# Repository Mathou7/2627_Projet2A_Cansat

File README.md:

# 2627_Projet2A_Cansat

Projet Cansat de 2A

## Partie Info

### Tableau Récapitulatif des connexions entre composants

| Broche STM32 | Signal | Élément / Périphérique | Protocole / Rôle | Adresse I2C |
| --- | --- | --- | --- | --- |
| **PA0** | `PWM` | Connecteur Moteur | Sortie PWM (+5V) | — |
| **PA1** | `MesBat` | Mesure Batterie (Pont diviseur) | Entrée analogique (ADC) | — |
| **PA2** / **PA3** | `VCP_RX` / `VCP_TX` | ST-LINK / Liaison série (Virtual COM) | UART | — |
| **PA4** | `INT_IMU` | Centrale Inertielle **BNO055** | Interruption matérielle | **`0x29`** (ou `0x28`) |
| **PA5** | `INT_BARO` | Capteur de pression **BMP581** | Interruption matérielle | **`0x46`** (ou `0x47`) |
| **PB0** | `CS_SD` | Port MicroSD (Chip Select) | GPIO / SPI | — |
| **PB3** | `SPI_SCK` | Port MicroSD (Horloge SPI) | SPI (Horloge) | — |
| **PB4** | `MISO` | Port MicroSD (Master In Slave Out) | SPI | — |
| **PB5** | `MOSI` | Port MicroSD (Master Out Slave In) | SPI | — |
| **PA9** | `SCL` | Bus I2C Commun (**BNO055** & **BMP581**) | I2C (Horloge avec pull-up) | Partagé |
| **PA8** | `SDA` | Bus I2C Commun (**BNO055** & **BMP581**) | I2C (Données avec pull-up) | Partagé |
| **PG10** | `NRST` | Bouton de Reset / Réinitialisation | Reset matériel | — |
| **PA13** / **PA14** | `SWDIO` / `SWCLK` | Connecteur ST-LINK (Debug / Programmation) | SWD | — |

## Tableau Récapitulatif du RTOS

| Tâche FreeRTOS | Rôle | Périodicité / Déclenchement | Priorité | Taille de Pile |
| --- | --- | --- | --- | --- |
| **`SensorTask`** | Acquisition I2C de la centrale BNO055 et du baromètre BMP581 | Périodique rigoureuse (ex: **20 ms / 50 Hz**) | **Haute** (ou *Normal* haute) | 512 mots (*words*) |
| **`LoggingTask`** | Enregistrement des données sur la carte MicroSD via le bus SPI | Sur événement (bloquée en attente via une Queue) | **Basse** (*Below Normal*) | 512 mots (*words*) |
| **`ControlTask`** | Surveillance de la tension batterie (ADC) et gestion de la PWM moteur | Périodique (ex: **100 ms / 10 Hz**) | **Normale** (*Normal*) | 512 mots (*words*) |

## Pinout STM32G431KBT6

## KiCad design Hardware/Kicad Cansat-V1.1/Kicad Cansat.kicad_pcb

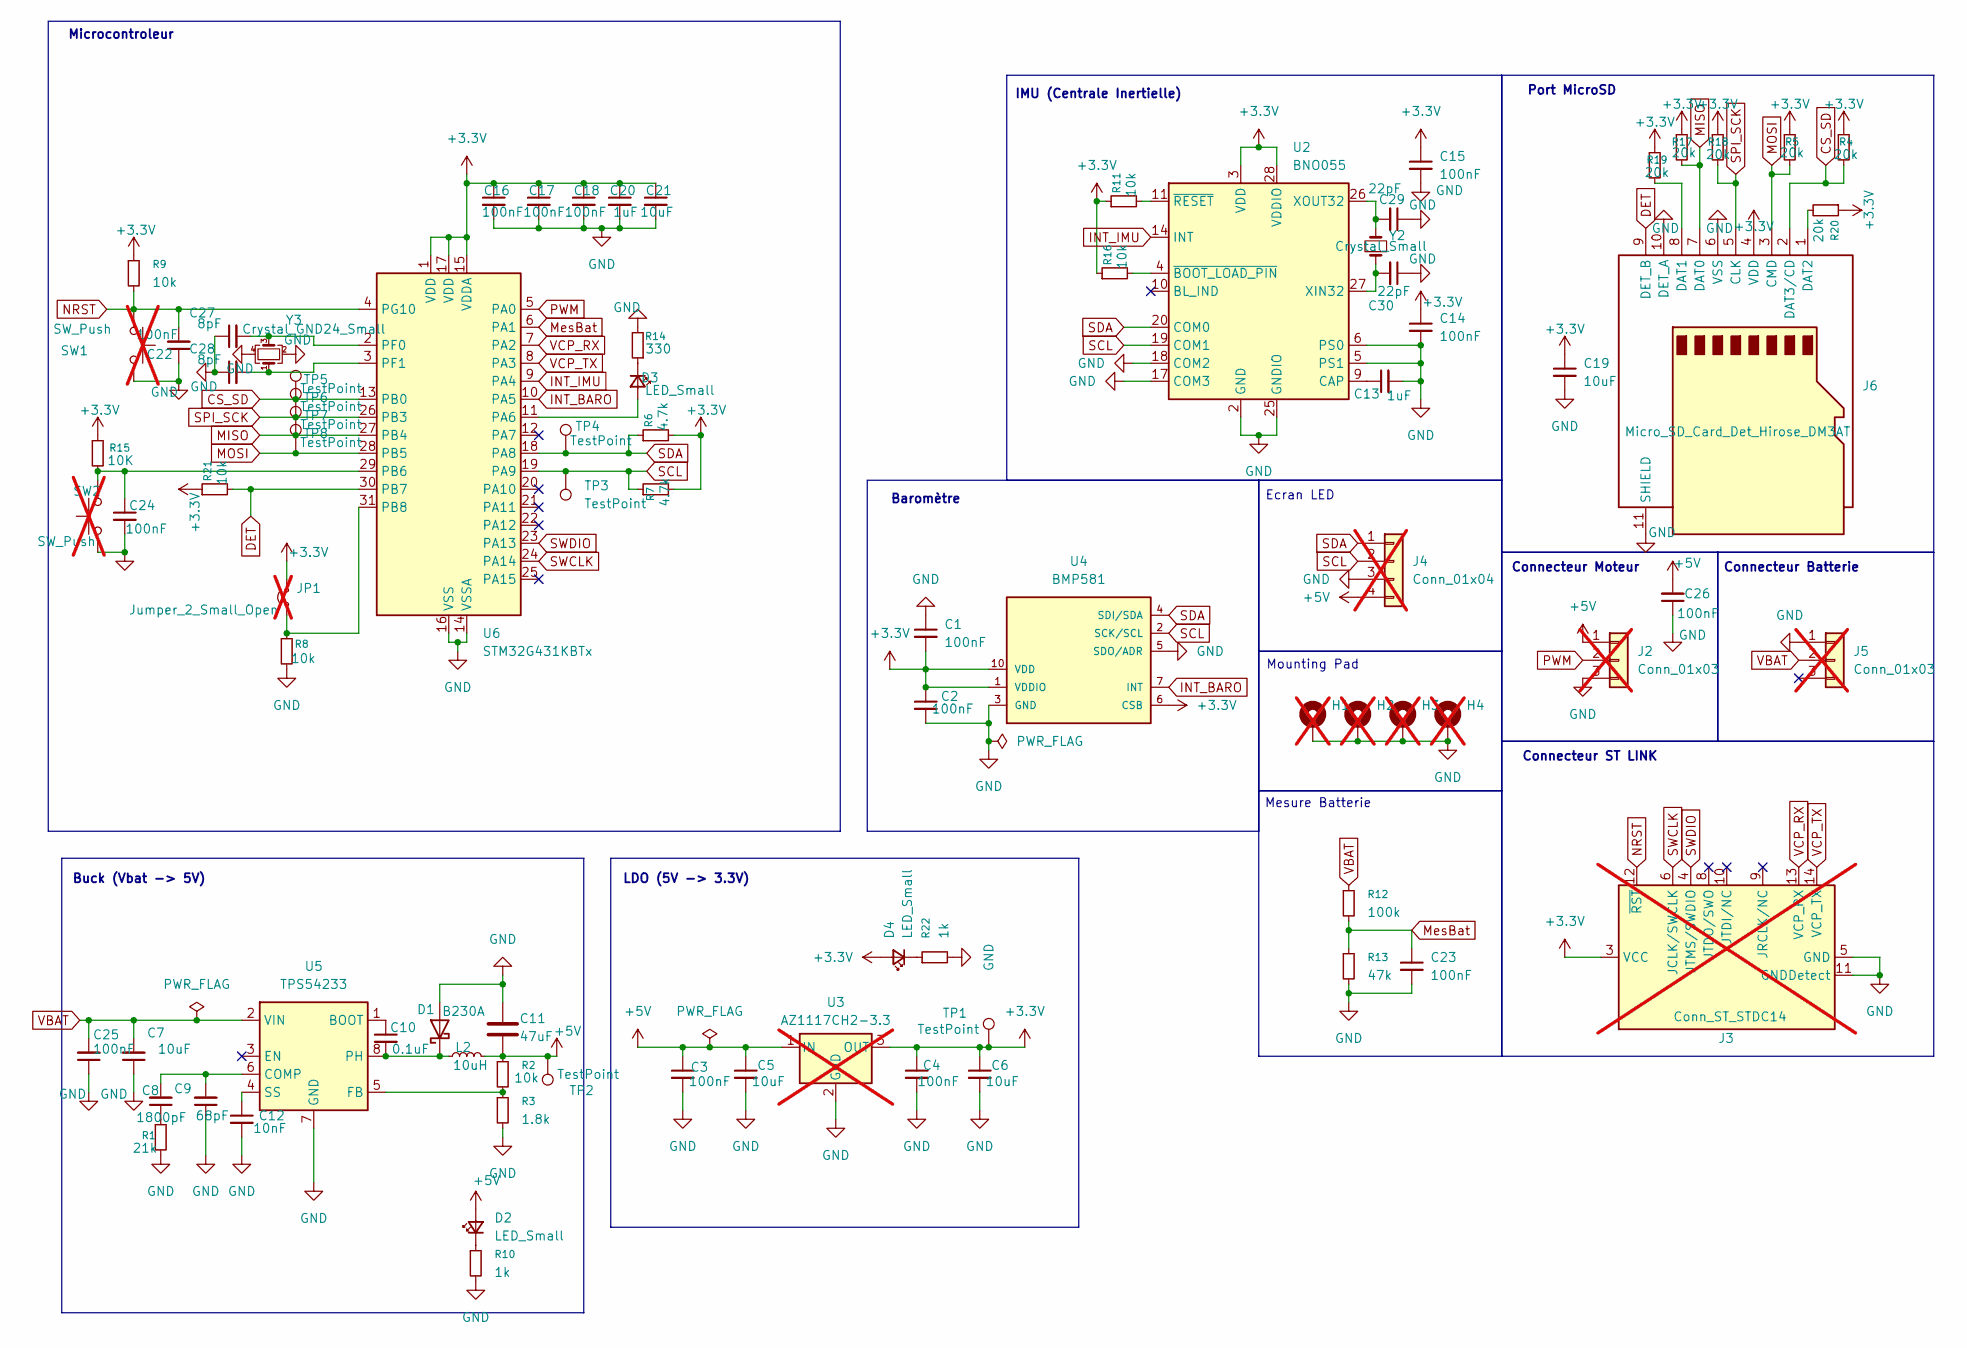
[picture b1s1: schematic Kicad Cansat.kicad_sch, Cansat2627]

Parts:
C1, C2, C3, C4, C14, C15, C16, C17, C18, C22, C23, C24, C25, C26: 100nF; C_0603_1608Metric; JLCPCB Part # C14663
C5, C6, C19, C21: 10uF; C_0603_1608Metric; JLCPCB Part # C19702
C7: 10uF; C_0805_2012Metric; JLCPCB Part # C15850
C8: 1800pF; C_0603_1608Metric; JLCPCB Part # C1604
C9: 68pF; C_0603_1608Metric; JLCPCB Part # C14858
C10: 0.1uF; C_0603_1608Metric; JLCPCB Part # C14663
C11: 47uF; C_1206_3216Metric; JLCPCB Part # C96123
C12: 10nF; C_0603_1608Metric; JLCPCB Part # C57112
C13, C20: 1uF; C_0603_1608Metric; JLCPCB Part # C15849
C27, C28: 8pF; C_0603_1608Metric; JLCPCB Part # C1634
C29, C30: 22pF; C_0603_1608Metric; JLCPCB Part # C1653
D1: B230A; D_SMA; JLCPCB Part # C22430
D2, D3, D4: LED_Small; LED_0603_1608Metric; JLCPCB Part # C2286
H1, H2, H3, H4: MountingHole_Pad; MountingHole_2.2mm_M2_DIN965_Pad; not fitted
J2, J5: Conn_01x03; JST_XH_B3B-XH-A_1x03_P2.50mm_Vertical; not fitted
J3: Conn_ST_STDC14; PinHeader_2x07_P1.27mm_Vertical_SMD; not fitted
J4: Conn_01x04; JST_XH_B4B-XH-A_1x04_P2.50mm_Vertical; not fitted
J6: Micro_SD_Card_Det_Hirose_DM3AT; microSD_HC_Hirose_DM3AT-SF-PEJM5; JLCPCB Part # C114218
JP1: Jumper_2_Small_Open; PinHeader_1x02_P2.54mm_Vertical; not fitted
L2: 10uH; L_Bourns-SRN4018; JLCPCB Part # C167121
R1: 21k; R_0603_1608Metric; JLCPCB Part # C31850
R2, R8, R9, R11, R16, R21: 10k; R_0603_1608Metric; JLCPCB Part # C25804
R3: 1.8k; R_0603_1608Metric; JLCPCB Part # C4177
R4, R5, R17, R18, R19, R20: 20k; R_0603_1608Metric; JLCPCB Part # C4184
R6, R7: 4.7k; R_0603_1608Metric; JLCPCB Part # C23162
R10, R22: 1k; R_0603_1608Metric; JLCPCB Part # C21190
R12: 100k; R_0603_1608Metric; JLCPCB Part # C25803
R13: 47k; R_0603_1608Metric; JLCPCB Part # C25819
R14: 330; R_0603_1608Metric; JLCPCB Part # C23025
R15: 10K; R_0603_1608Metric; JLCPCB Part # C25804
SW1, SW2: SW_Push; SW_PUSH_6mm_H5mm; not fitted
TP1, TP2, TP3, TP4, TP5, TP6, TP7, TP8: TestPoint; TestPoint_Pad_D1.0mm
U2: BNO055; LGA-28_5.2x3.8mm_P0.5mm; JLCPCB Part # C93216
U3: AZ1117CH2-3.3; SOT-223-3_TabPin2; JLCPCB Part # C108492; not fitted
U4: BMP581; JLCPCB Part # C5362283
U5: TPS54233; SOIC-8_3.9x4.9mm_P1.27mm; JLCPCB Part # C2873169
U6: STM32G431KBTx; LQFP-32_7x7mm_P0.8mm; JLCPCB Part # C5270317
Y2: Crystal_Small; Crystal_SMD_3215-2Pin_3.2x1.5mm; JLCPCB Part # C252398
Y3: Crystal_GND24_Small; Crystal_SMD_3225-4Pin_3.2x2.5mm; JLCPCB Part # C1985466

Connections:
+3.3V: C1.2, C2.1, C4.1, C6.1, C14.1, C15.1, C16.1, C17.1, C18.1, C19.1, C20.1, C21.1, D4.2 (A), J3.3 (VCC), J6.4 (VDD), JP1.2 (B), R4.1, R5.1, R6.2, R7.2, R9.1, R11.1, R15.1, R16.1, R17.1, R18.1, R19.1, R20.1, R21.1, TP1.1, U2.3 (VDD), U2.28 (VDDIO), U3.3 (OUT), U4.1 (VDDIO), U4.6 (CSB), U4.10 (VDD), U6.1 (VDD), U6.15 (VDDA), U6.17 (VDD)
+5V: C3.1, C5.1, C11.2, C26.2, D2.2 (A), J2.1, J4.4, L2.2, R2.1, TP2.1, U3.1 (IN)
CS_SD: J6.2 (DAT3/CD), R4.2, TP5.1, U6.13 (PB0)
DET: J6.9 (DET_B), R21.2, U6.30 (PB7)
GND: C1.1, C2.2, C3.2, C4.2, C5.2, C6.2, C7.1, C9.1, C11.1, C12.2, C13.2, C14.2, C15.2, C16.2, C17.2, C18.2, C19.2, C20.2, C21.2, C22.1, C23.2, C24.2, C25.1, C26.1, C27.1, C28.1, C29.1, C30.1, D1.2 (A), H1.1, H2.1, H3.1, H4.1, J2.3, J3.5 (GND), J3.7 (GND), J3.11 (GNDDetect), J4.3, J5.1, J6.6 (VSS), J6.10 (DET_A), J6.11 (SHIELD), R1.2, R3.2, R8.2, R10.2, R13.2, R14.2, R22.2, SW1.2, SW2.1, U2.2 (GND), U2.5 (PS1), U2.6 (PS0), U2.17 (COM3), U2.18 (COM2), U2.25 (GNDIO), U3.2 (GND), U4.3 (GND), U4.5 (SDO/ADR), U4.8 (GND), U4.9 (GND), U5.7 (GND), U6.14 (VSSA), U6.16 (VSS), U6.32 (VSS), Y3.2, Y3.4
INT_BARO: U4.7 (INT), U6.10 (PA5)
INT_IMU: U2.14 (INT), U6.9 (PA4)
MISO: J6.7 (DAT0), R17.2, TP7.1, U6.27 (PB4)
MOSI: J6.3 (CMD), R5.2, TP8.1, U6.28 (PB5)
MesBat: C23.1, R12.2, R13.1, U6.6 (PA1)
NRST: C22.2, J3.12 (~RST), R9.2, SW1.1, U6.4 (PG10)
unnamed: C8.1, R1.1
unnamed: C10.2, D1.1 (K), L2.1, U5.8 (PH)
unnamed: D2.1 (K), R10.1
unnamed: D3.2 (A), U6.11 (PA6)
unnamed: D3.1 (K), R14.1
unnamed: D4.1 (K), R22.1
unnamed: J6.8 (DAT1), R19.2
unnamed: J6.1 (DAT2), R20.2
unnamed: JP1.1 (A), R8.1, U6.31 (PB8)
unnamed: C13.1, U2.9 (CAP)
unnamed: C30.2, U2.27 (XIN32), Y2.1
unnamed: C29.2, U2.26 (XOUT32), Y2.2
unnamed: R16.2, U2.4 (~BOOT_LOAD_PIN)
unnamed: R11.2, U2.11 (~RESET)
unnamed: C10.1, U5.1 (BOOT)
unnamed: C8.2, C9.2, U5.6 (COMP)
unnamed: R2.2, R3.1, U5.5 (FB)
unnamed: C12.1, U5.4 (SS)
unnamed: C24.1, R15.2, SW2.2, U6.29 (PB6)
unnamed: C27.2, U6.2 (PF0), Y3.3
unnamed: C28.2, U6.3 (PF1), Y3.1
PWM: J2.2, U6.5 (PA0)
SCL: J4.2, R7.1, TP3.1, U2.19 (COM1), U4.2 (SCK/SCL), U6.19 (PA9)
SDA: J4.1, R6.1, TP4.1, U2.20 (COM0), U4.4 (SDI/SDA), U6.18 (PA8)
SPI_SCK: J6.5 (CLK), R18.2, TP6.1, U6.26 (PB3)
SWCLK: J3.6 (JCLK/SWCLK), U6.24 (PA14)
SWDIO: J3.4 (JTMS/SWDIO), U6.23 (PA13)
VBAT: C7.2, C25.2, J5.2, R12.1, U5.2 (VIN)
VCP_RX: J3.13 (VCP_RX), U6.7 (PA2)
VCP_TX: J3.14 (VCP_TX), U6.8 (PA3)

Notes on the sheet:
IMU (Centrale Inertielle)
Buck (Vbat -> 5V)
Baromètre
Connecteur ST LINK
Mounting Pad
Connecteur Batterie
LDO (5V -> 3.3V)
Microcontroleur
Mesure Batterie
Port MicroSD
Connecteur Moteur
Ecran LED

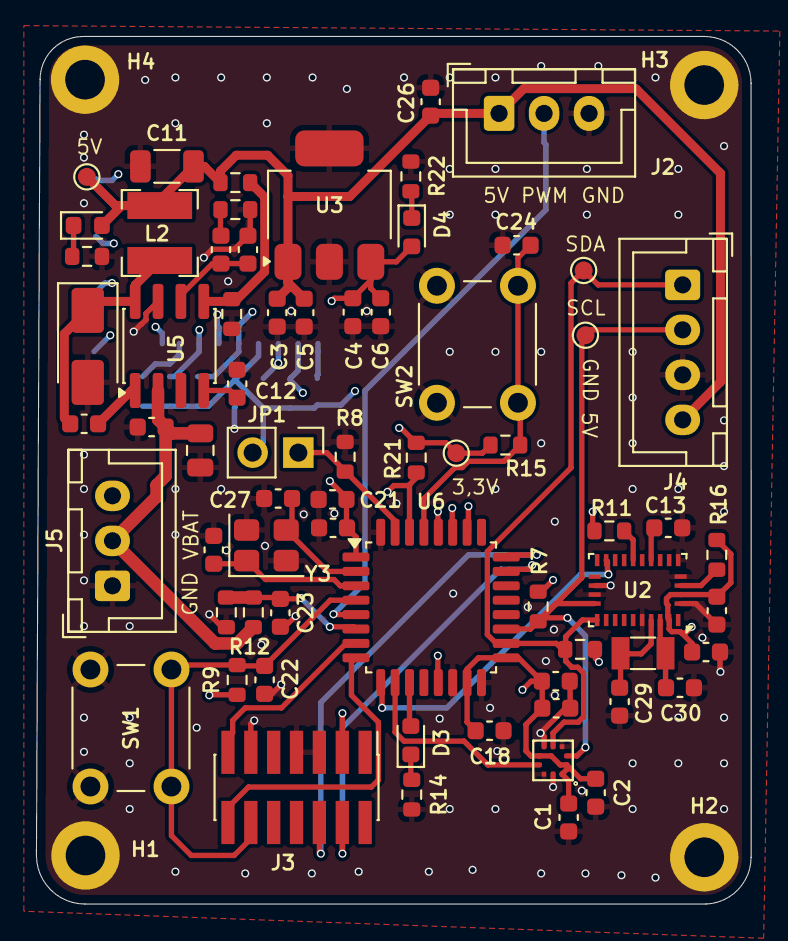
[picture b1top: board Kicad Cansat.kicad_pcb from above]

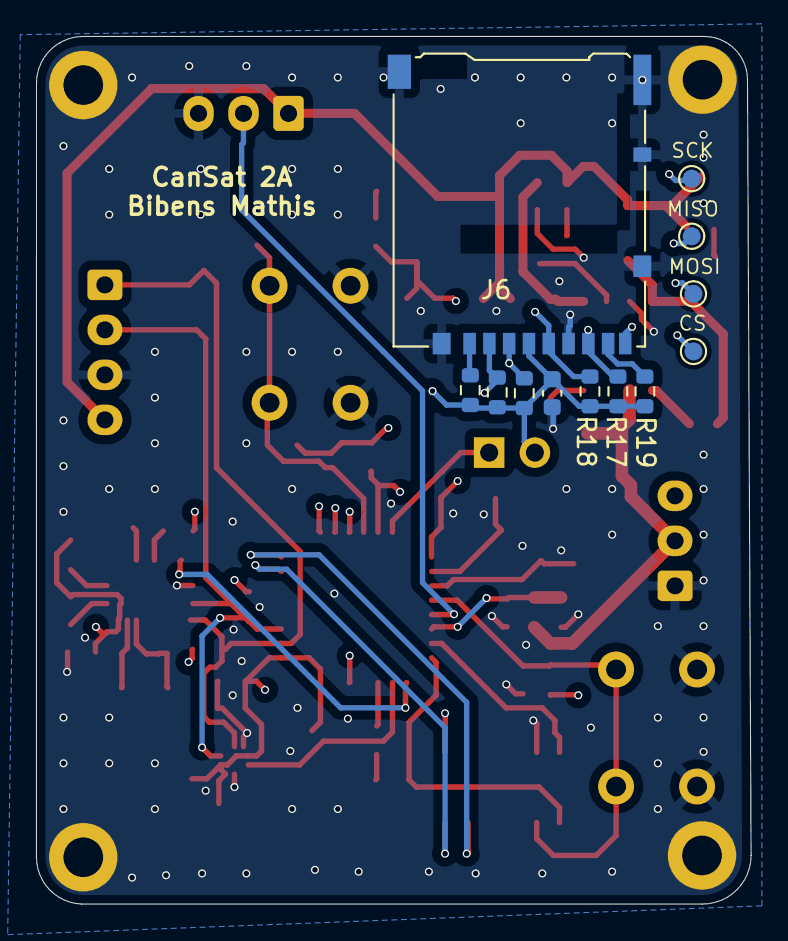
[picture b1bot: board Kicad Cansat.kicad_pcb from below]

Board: 6 copper layers, 39.7 x 48.2 mm, 84 parts (12 on the bottom side), 41 nets.
